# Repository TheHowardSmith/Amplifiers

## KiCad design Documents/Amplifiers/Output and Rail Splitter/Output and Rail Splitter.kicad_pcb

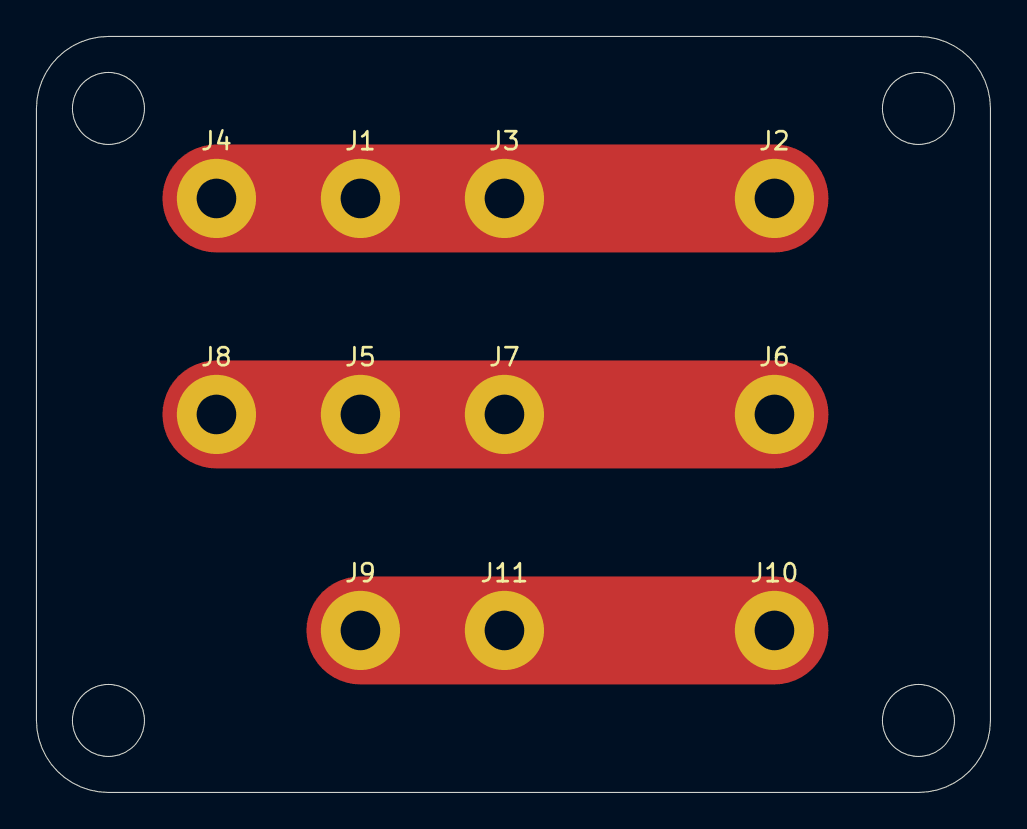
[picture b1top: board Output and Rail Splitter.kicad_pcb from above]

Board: 2 copper layers, 53.0 x 42.0 mm, 11 parts (0 on the bottom side), 3 nets.

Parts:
J1: +24V_L; MountingHole_2.2mm_M2_Pad
J2: +24V_in; MountingHole_2.2mm_M2_Pad
J3: +24V_R; MountingHole_2.2mm_M2_Pad
J4: +24V_vol; MountingHole_2.2mm_M2_Pad
J5: GND_L; MountingHole_2.2mm_M2_Pad
J6: GND_in; MountingHole_2.2mm_M2_Pad
J7: GND_R; MountingHole_2.2mm_M2_Pad
J8: GND_vol; MountingHole_2.2mm_M2_Pad
J9: -24V_L; MountingHole_2.2mm_M2_Pad
J10: -24V_in; MountingHole_2.2mm_M2_Pad
J11: -24V_R; MountingHole_2.2mm_M2_Pad

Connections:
unnamed: J1.1, J2.1, J3.1, J4.1
unnamed: J5.1, J6.1, J7.1, J8.1
unnamed: J9.1, J10.1, J11.1

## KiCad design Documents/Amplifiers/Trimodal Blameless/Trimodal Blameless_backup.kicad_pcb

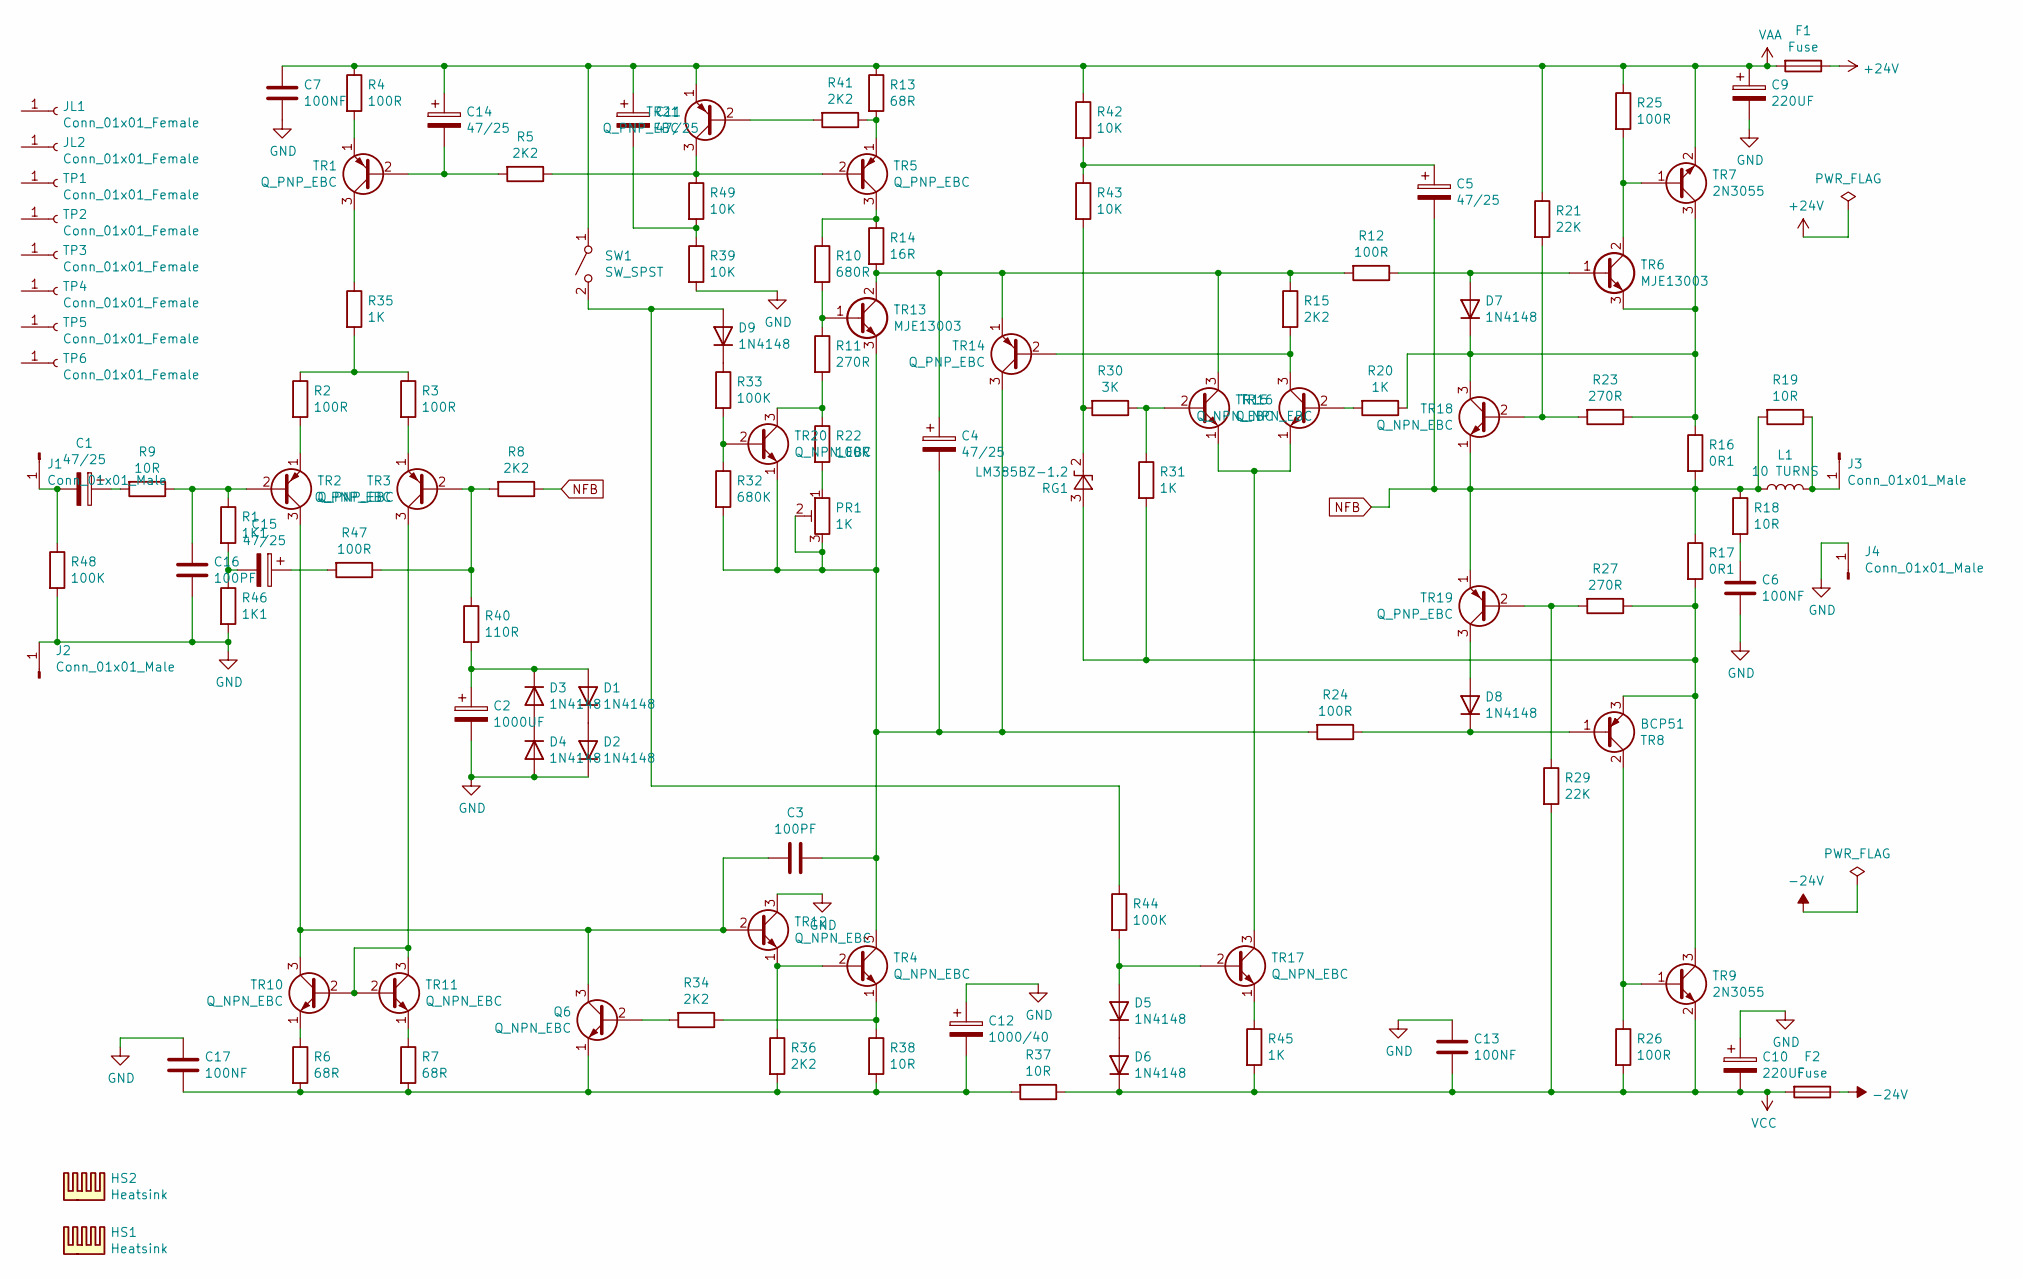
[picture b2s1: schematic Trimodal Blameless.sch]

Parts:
C1, C4, C5, C11, C14, C15: 47/25; CP_Radial_D8.0mm_P5.00mm
C2: 1000UF; CP_Radial_D10.0mm_P5.00mm
C3, C16: 100PF; C_Disc_D4.3mm_W1.9mm_P5.00mm
C6, C7, C13, C17: 100NF; C_Rect_L11.0mm_W3.5mm_P10.00mm_MKT
C9, C10: 220UF; CP_Radial_D10.0mm_P5.00mm
C12: 1000/40; CP_Radial_D12.5mm_P5.00mm
D1, D2, D3, D4, D5, D6, D7, D8, D9: 1N4148; D_DO-41_SOD81_P7.62mm_Horizontal
F1, F2: Fuse; Fuseholder_Cylinder-5x20mm_Stelvio-Kontek_PTF78_Horizontal_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
HS1, HS2: Heatsink; Heatsink_Fischer_SK104-STCB_35x13mm__2xDrill3.5mm_ScrewM3
J1, J2, J3, J4: Conn_01x01_Male; Pin_D1.3mm_L11.0mm
JL1, JL2: Conn_01x01_Female; Pin_D1.3mm_L11.0mm
L1: 10 TURNS; L_Axial_L20.3mm_D12.7mm_P25.40mm_Horizontal_Vishay_IHA-201
PR1: 1K; Potentiometer_ACP_CA9-V10_Vertical
Q6: Q_NPN_EBC; TO-92
R1, R46: 1K1; R_Axial_DIN0207_L6.3mm_D2.5mm_P10.16mm_Horizontal
R2, R3, R4, R12, R22, R24, R25, R26, R47: 100R; R_Axial_DIN0207_L6.3mm_D2.5mm_P10.16mm_Horizontal
R5, R8, R15, R34, R36, R41: 2K2; R_Axial_DIN0207_L6.3mm_D2.5mm_P10.16mm_Horizontal
R6, R7, R13: 68R; R_Axial_DIN0207_L6.3mm_D2.5mm_P10.16mm_Horizontal
R9, R18, R19, R37, R38: 10R; R_Axial_DIN0207_L6.3mm_D2.5mm_P10.16mm_Horizontal
R10: 680R; R_Axial_DIN0207_L6.3mm_D2.5mm_P10.16mm_Horizontal
R11, R23, R27: 270R; R_Axial_DIN0207_L6.3mm_D2.5mm_P10.16mm_Horizontal
R14: 16R; R_Axial_DIN0207_L6.3mm_D2.5mm_P10.16mm_Horizontal
R16, R17: 0R1; R_Axial_DIN0922_L20.0mm_D9.0mm_P30.48mm_Horizontal
R20, R31, R35, R45: 1K; R_Axial_DIN0207_L6.3mm_D2.5mm_P10.16mm_Horizontal
R21, R29: 22K; R_Axial_DIN0207_L6.3mm_D2.5mm_P10.16mm_Horizontal
R30: 3K; R_Axial_DIN0207_L6.3mm_D2.5mm_P10.16mm_Horizontal
R32: 680K; R_Axial_DIN0207_L6.3mm_D2.5mm_P10.16mm_Horizontal
R33, R44, R48: 100K; R_Axial_DIN0207_L6.3mm_D2.5mm_P10.16mm_Horizontal
R39, R42, R43, R49: 10K; R_Axial_DIN0207_L6.3mm_D2.5mm_P10.16mm_Horizontal
R40: 110R; R_Axial_DIN0207_L6.3mm_D2.5mm_P10.16mm_Horizontal
RG1: LM385BZ-1.2; TO-92_Inline
SW1: SW_SPST; SW_NKK_G1xJP
TP1, TP2, TP3, TP4, TP5, TP6: Conn_01x01_Female; Pin_D1.3mm_L11.0mm
TR1, TR2, TR3, TR5, TR14, TR19, TR21: Q_PNP_EBC; TO-92
TR4, TR10, TR11, TR12, TR15, TR16, TR17, TR18, TR20: Q_NPN_EBC; TO-92
TR6, TR13: MJE13003; TO-126-3_Vertical
TR7, TR9: 2N3055; TO-3
TR8: BCP51; TO-126-3_Vertical

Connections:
+24V: F1.1
-24V: F2.1
GND: C2.2, C6.2, C7.2, C9.2, C10.1, C12.1, C13.1, C16.2, C17.1, D2.1 (K), D4.2 (A), J2.1, J4.1, R39.2, R46.2, R48.2, TR12.3 (C)
NFB: C5.2, L1.1, R8.1, R16.2, R17.1, R18.1, R19.2, TR18.1 (E), TR19.1 (E)
unnamed: C1.1, R9.2
unnamed: C1.2, J1.1, R48.1
unnamed: C2.1, D1.2 (A), D3.1 (K), R40.2
unnamed: C3.1, C4.2, PR1.2, PR1.3, R24.2, R32.2, TR4.3 (C), TR13.3 (E), TR14.3 (C), TR20.1 (E)
unnamed: C3.2, Q6.3 (C), TR2.3 (C), TR10.3 (C), TR12.2 (B)
unnamed: C4.1, R12.2, R14.2, R15.1, TR13.2 (C), TR14.1 (E), TR15.3 (C)
unnamed: C5.1, R42.2, R43.1
unnamed: C6.1, R18.2
unnamed: C11.2, R39.1, R49.2
unnamed: C12.2, C17.2, Q6.1 (E), R6.2, R7.2, R36.2, R37.2, R38.2
unnamed: C14.2, R5.2, TR1.2 (B)
unnamed: C15.1, R47.2
unnamed: C15.2, R1.2, R46.1
unnamed: C16.1, R1.1, R9.1, TR2.2 (B)
unnamed: D1.1 (K), D2.2 (A)
unnamed: D3.2 (A), D4.1 (K)
unnamed: D5.1 (K), D6.2 (A)
unnamed: D5.2 (A), R44.2, TR17.2 (B)
unnamed: D7.1 (K), R16.1, R20.1, R23.1, TR6.3 (E), TR7.3 (C), TR18.3 (C)
unnamed: D7.2 (A), R12.1, TR6.1 (B)
unnamed: D8.1 (K), R24.1, TR8.1 (B)
unnamed: D8.2 (A), TR19.3 (C)
unnamed: D9.1 (K), R33.1
unnamed: D9.2 (A), R44.1, SW1.2 (B)
unnamed: J3.1, L1.2, R19.1
unnamed: PR1.1, R22.2
unnamed: Q6.2 (B), R34.2
unnamed: R2.1, R3.1, R35.2
unnamed: R2.2, TR2.1 (E)
unnamed: R3.2, TR3.1 (E)
unnamed: R4.2, TR1.1 (E)
unnamed: R6.1, TR10.1 (E)
unnamed: R7.1, TR11.1 (E)
unnamed: R10.1, R14.1, TR5.3 (C)
unnamed: R10.2, R11.1, TR13.1 (B)
unnamed: R11.2, R22.1, TR20.3 (C)
unnamed: R13.2, R41.1, TR5.1 (E)
unnamed: R15.2, TR14.2 (B), TR16.3 (C)
unnamed: R17.2, R27.1, R31.2, RG1.3 (A), TR8.3 (E), TR9.3 (C)
unnamed: R20.2, TR16.2 (B)
unnamed: R21.2, R23.2, TR18.2 (B)
unnamed: R25.2, TR6.2 (C), TR7.1 (B)
unnamed: R26.1, TR8.2 (C), TR9.1 (B)
unnamed: R27.2, R29.1, TR19.2 (B)
unnamed: R30.1, R31.1, TR15.2 (B)
unnamed: R30.2, R43.2, RG1.2 (K)
unnamed: R32.1, R33.2, TR20.2 (B)
unnamed: R34.1, R38.1, TR4.1 (E)
unnamed: R35.1, TR1.3 (C)
unnamed: R36.1, TR4.2 (B), TR12.1 (E)
unnamed: R8.2, R40.1, R47.1, TR3.2 (B)
unnamed: R41.2, TR21.2 (B)
unnamed: R45.1, TR17.1 (E)
unnamed: R5.1, R49.1, TR5.2 (B), TR21.3 (C)
unnamed: TR3.3 (C), TR10.2 (B), TR11.2 (B), TR11.3 (C)
unnamed: TR15.1 (E), TR16.1 (E), TR17.3 (C)
VAA: C7.1, C9.1, C11.1, C14.1, F1.2, R4.1, R13.1, R21.1, R25.1, R42.1, SW1.1 (A), TR7.2 (E), TR21.1 (E)
VCC: C10.2, C13.2, D6.1 (K), F2.2, R26.2, R29.2, R37.1, R45.2, TR9.2 (E)

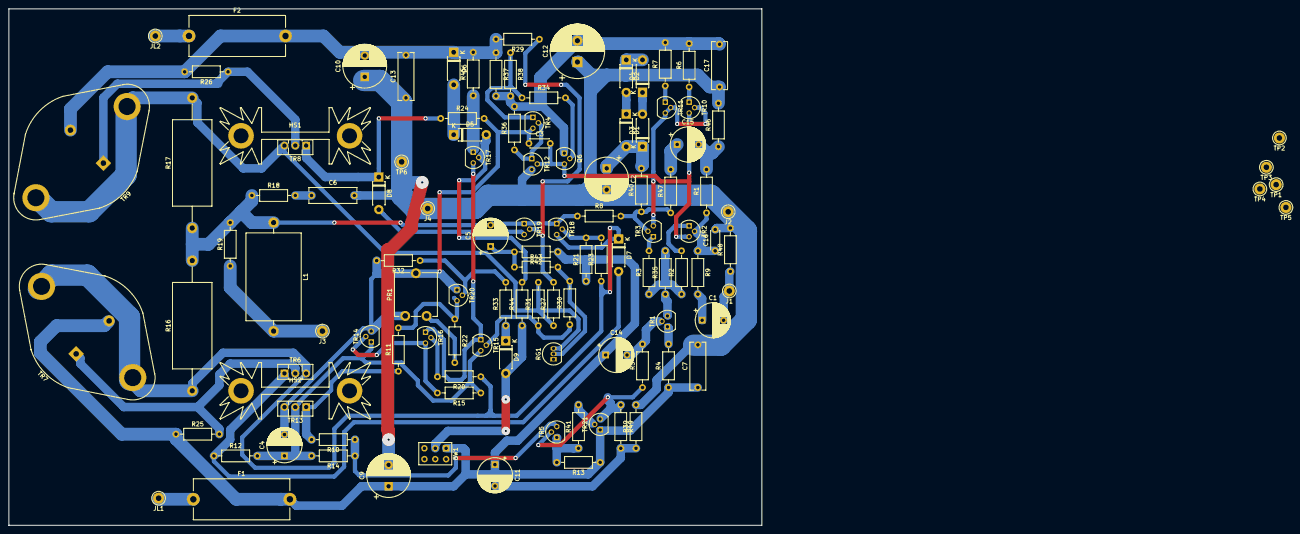
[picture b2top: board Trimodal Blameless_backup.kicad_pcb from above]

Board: 2 copper layers, 176.3 x 120.9 mm, 115 parts (0 on the bottom side), 60 nets.

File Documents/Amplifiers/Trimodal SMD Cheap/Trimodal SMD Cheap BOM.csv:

Comment,Designator,Footprint,LCSC
220UF,"C10,C9",Capacitor_SMD:CP_Elec_10x10,C176670
47/25,"C14,C1,C15,C11,C4,C5",Capacitor_Tantalum_SMD:CP_EIA-7343-31_Kemet-D,C117039
100PF,"C16,C3",Capacitor_SMD:C_0805_2012Metric,C1790
100NF,"C7,C17,C6,C13",Capacitor_SMD:C_0805_2012Metric,C49678
1N4148,"D3,D4,D1,D2,D9,D6,D5,D7,D8",Diode_SMD:D_SOD-123,C81598
1K1,"R1,R46",Resistor_SMD:R_0603_1608Metric,C22764
680R,R10,Resistor_SMD:R_0805_2012Metric,C17798
270R,"R11,R23,R27",Resistor_SMD:R_0805_2012Metric,C17590
16R,R14,Resistor_SMD:R_0805_2012Metric,C17491
0R1,"R16,R17,R166,R177",Resistor_SMD:R_2512_6332Metric,C78195
22K,"R21,R29",Resistor_SMD:R_0805_2012Metric,C17560
3K,R30,Resistor_SMD:R_0805_2012Metric,C17661
680K,R32,Resistor_SMD:R_0805_2012Metric,C17797
1K,"R35,R45,R31,R20",Resistor_SMD:R_0805_2012Metric,C17513
100R,"R4,R2,R3,R47,R24,R12,R25,R26,R22",Resistor_SMD:R_0805_2012Metric,C17408
110R,R40,Resistor_SMD:R_0805_2012Metric,C17423
100K,"R48,R33,R44",Resistor_SMD:R_0805_2012Metric,C17407
10K,"R49,R39,R42,R43",Resistor_SMD:R_0805_2012Metric,C17414
2K2,"R5,R8,R41,R36,R34,R15",Resistor_SMD:R_0805_2012Metric,C17520
68R,"R6,R7,R13",Resistor_SMD:R_0805_2012Metric,C17802
10R,"R9,R38,R37,R18,R19",Resistor_SMD:R_0805_2012Metric,C17415
LM385M3X-2.5,RG1,Package_TO_SOT_SMD:SOT-23,C83345
SW_SPST,SW1,Package_SO:SOP-4_3.8x4.1mm_P2.54mm,C99477
Q_PNP_EBC,"TR1,TR3,TR2,TR21,TR5,TR14,TR19",Package_TO_SOT_SMD:SOT-89-3,C47787
Q_NPN_EBC,"TR10,TR11,TR20,TR4,TR12,Q6,TR15,TR16,TR18,TR17",Package_TO_SOT_SMD:SOT-89-3,C100026

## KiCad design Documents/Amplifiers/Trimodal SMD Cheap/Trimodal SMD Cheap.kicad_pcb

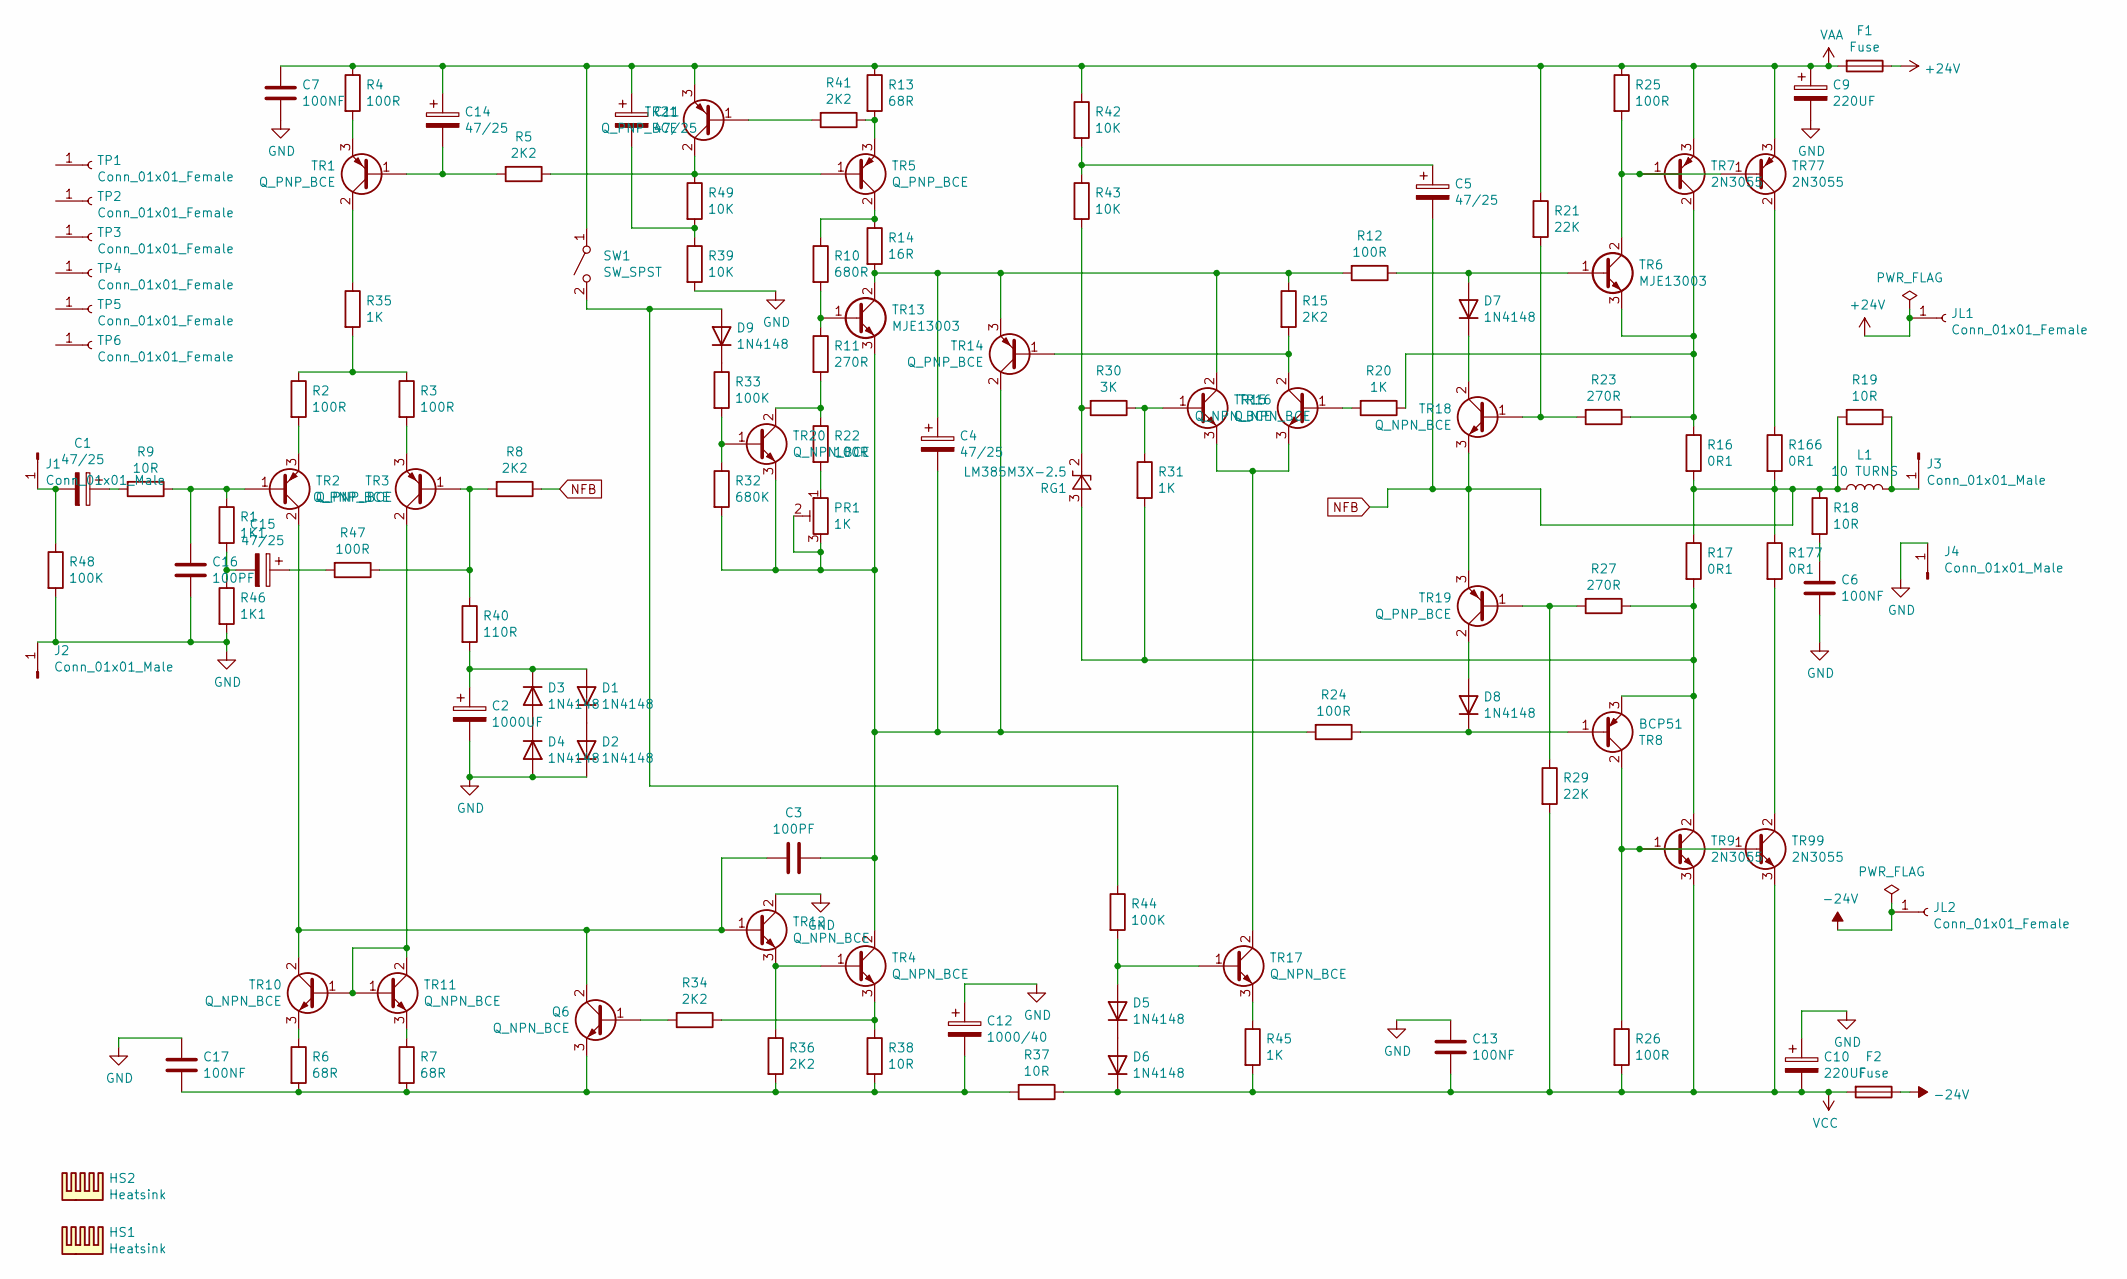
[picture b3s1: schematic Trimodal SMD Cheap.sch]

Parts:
C1, C4, C5, C11, C14, C15: 47/25; CP_EIA-7343-31_Kemet-D
C2: 1000UF; CP_Radial_D12.5mm_P5.00mm
C3, C16: 100PF; C_0805_2012Metric
C6, C7, C13, C17: 100NF; C_0805_2012Metric
C9, C10: 220UF; CP_Elec_10x10
C12: 1000/40; CP_Radial_D12.5mm_P5.00mm
D1, D2, D3, D4, D5, D6, D7, D8, D9: 1N4148; D_SOD-123
F1, F2: Fuse; Fuseholder_Cylinder-5x20mm_Stelvio-Kontek_PTF78_Horizontal_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
HS1, HS2: Heatsink; Heatsink_Fischer_SK104-STCB_35x13mm__2xDrill3.5mm_ScrewM3
J1, J2: Conn_01x01_Male; Pin_D1.3mm_L11.0mm
J3, J4: Conn_01x01_Male; MountingHole_2.2mm_M2_Pad
JL1, JL2: Conn_01x01_Female; MountingHole_2.2mm_M2_Pad
L1: 10 TURNS; L_Axial_L20.3mm_D12.7mm_P25.40mm_Horizontal_Vishay_IHA-201
PR1: 1K; Potentiometer_ACP_CA9-V10_Vertical
Q6: Q_NPN_BCE; SOT-89-3
R1, R46: 1K1; R_0805_2012Metric
R2, R3, R4, R12, R22, R24, R25, R26, R47: 100R; R_0805_2012Metric
R5, R8, R15, R34, R36, R41: 2K2; R_0805_2012Metric
R6, R7, R13: 68R; R_0805_2012Metric
R9, R18, R19, R37, R38: 10R; R_0805_2012Metric
R10: 680R; R_0805_2012Metric
R11, R23, R27: 270R; R_0805_2012Metric
R14: 16R; R_0805_2012Metric
R16, R17, R166, R177: 0R1; R_2512_6332Metric
R20, R31, R35, R45: 1K; R_0805_2012Metric
R21, R29: 22K; R_0805_2012Metric
R30: 3K; R_0805_2012Metric
R32: 680K; R_0805_2012Metric
R33, R44, R48: 100K; R_0805_2012Metric
R39, R42, R43, R49: 10K; R_0805_2012Metric
R40: 110R; R_0805_2012Metric
RG1: LM385M3X-2.5; SOT-23
SW1: SW_SPST; SOP-4_3.8x4.1mm_P2.54mm
TP1, TP2: Conn_01x01_Female; Pin_D1.3mm_L11.0mm
TP3, TP4, TP5, TP6: Conn_01x01_Female; MountingHole_2.2mm_M2_Pad
TR1, TR2, TR3, TR5, TR14, TR19, TR21: Q_PNP_BCE; SOT-89-3
TR4, TR10, TR11, TR12, TR15, TR16, TR17, TR18, TR20: Q_NPN_BCE; SOT-89-3
TR6, TR13: MJE13003; TO-126-3_Vertical
TR7, TR9, TR77, TR99: 2N3055; TO-3P-3_Vertical
TR8: BCP51; TO-126-3_Vertical

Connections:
+24V: F1.1, JL1.1
-24V: F2.1, JL2.1
GND: C2.2, C6.2, C7.2, C9.2, C10.1, C12.1, C13.1, C16.2, C17.1, D2.1 (K), D4.2 (A), J2.1, J4.1, R39.2, R46.2, R48.2, TR12.2 (C)
NFB: C5.2, L1.1, R8.1, R16.2, R17.1, R18.1, R19.2, R166.2, R177.1, TR18.3 (E), TR19.3 (E)
unnamed: C1.1, R9.2
unnamed: C1.2, J1.1, R48.1
unnamed: C2.1, D1.2 (A), D3.1 (K), R40.2
unnamed: C3.1, C4.2, PR1.2, PR1.3, R24.2, R32.2, TR4.2 (C), TR13.3 (E), TR14.2 (C), TR20.3 (E)
unnamed: C3.2, Q6.2 (C), TR2.2 (C), TR10.2 (C), TR12.1 (B)
unnamed: C4.1, R12.2, R14.2, R15.1, TR13.2 (C), TR14.3 (E), TR15.2 (C)
unnamed: C5.1, R42.2, R43.1
unnamed: C6.1, R18.2
unnamed: C11.2, R39.1, R49.2
unnamed: C12.2, C17.2, Q6.3 (E), R6.2, R7.2, R36.2, R37.2, R38.2
unnamed: C14.2, R5.2, TR1.1 (B)
unnamed: C15.1, R47.2
unnamed: C15.2, R1.2, R46.1
unnamed: C16.1, R1.1, R9.1, TR2.1 (B)
unnamed: D1.1 (K), D2.2 (A)
unnamed: D3.2 (A), D4.1 (K)
unnamed: D5.1 (K), D6.2 (A)
unnamed: D5.2 (A), R44.2, TR17.1 (B)
unnamed: D7.1 (K), TR18.2 (C)
unnamed: D7.2 (A), R12.1, TR6.1 (B)
unnamed: D8.1 (K), R24.1, TR8.1 (B)
unnamed: D8.2 (A), TR19.2 (C)
unnamed: D9.1 (K), R33.1
unnamed: D9.2 (A), R44.1, SW1.2 (B)
unnamed: J3.1, L1.2, R19.1
unnamed: PR1.1, R22.2
unnamed: Q6.1 (B), R34.2
unnamed: R2.1, R3.1, R35.2
unnamed: R2.2, TR2.3 (E)
unnamed: R3.2, TR3.3 (E)
unnamed: R4.2, TR1.3 (E)
unnamed: R6.1, TR10.3 (E)
unnamed: R7.1, TR11.3 (E)
unnamed: R10.1, R14.1, TR5.2 (C)
unnamed: R10.2, R11.1, TR13.1 (B)
unnamed: R11.2, R22.1, TR20.2 (C)
unnamed: R13.2, R41.1, TR5.3 (E)
unnamed: R15.2, TR14.1 (B), TR16.2 (C)
unnamed: R16.1, R20.1, R23.1, TR6.3 (E), TR7.2 (C)
unnamed: R17.2, R27.1, R31.2, RG1.3 (A), TR8.3 (E), TR9.2 (C)
unnamed: R20.2, TR16.1 (B)
unnamed: R21.2, R23.2, TR18.1 (B)
unnamed: R25.2, TR6.2 (C), TR7.1 (B), TR77.1 (B)
unnamed: R26.1, TR8.2 (C), TR9.1 (B), TR99.1 (B)
unnamed: R27.2, R29.1, TR19.1 (B)
unnamed: R30.1, R31.1, TR15.1 (B)
unnamed: R30.2, R43.2, RG1.2 (K)
unnamed: R32.1, R33.2, TR20.1 (B)
unnamed: R34.1, R38.1, TR4.3 (E)
unnamed: R35.1, TR1.2 (C)
unnamed: R36.1, TR4.1 (B), TR12.3 (E)
unnamed: R8.2, R40.1, R47.1, TR3.1 (B)
unnamed: R41.2, TR21.1 (B)
unnamed: R45.1, TR17.3 (E)
unnamed: R5.1, R49.1, TR5.1 (B), TR21.2 (C)
unnamed: R166.1, TR77.2 (C)
unnamed: R177.2, TR99.2 (C)
unnamed: TR3.2 (C), TR10.1 (B), TR11.1 (B), TR11.2 (C)
unnamed: TR15.3 (E), TR16.3 (E), TR17.2 (C)
VAA: C7.1, C9.1, C11.1, C14.1, F1.2, R4.1, R13.1, R21.1, R25.1, R42.1, SW1.1 (A), TR7.3 (E), TR21.3 (E), TR77.3 (E)
VCC: C10.2, C13.2, D6.1 (K), F2.2, R26.2, R29.2, R37.1, R45.2, TR9.3 (E), TR99.3 (E)

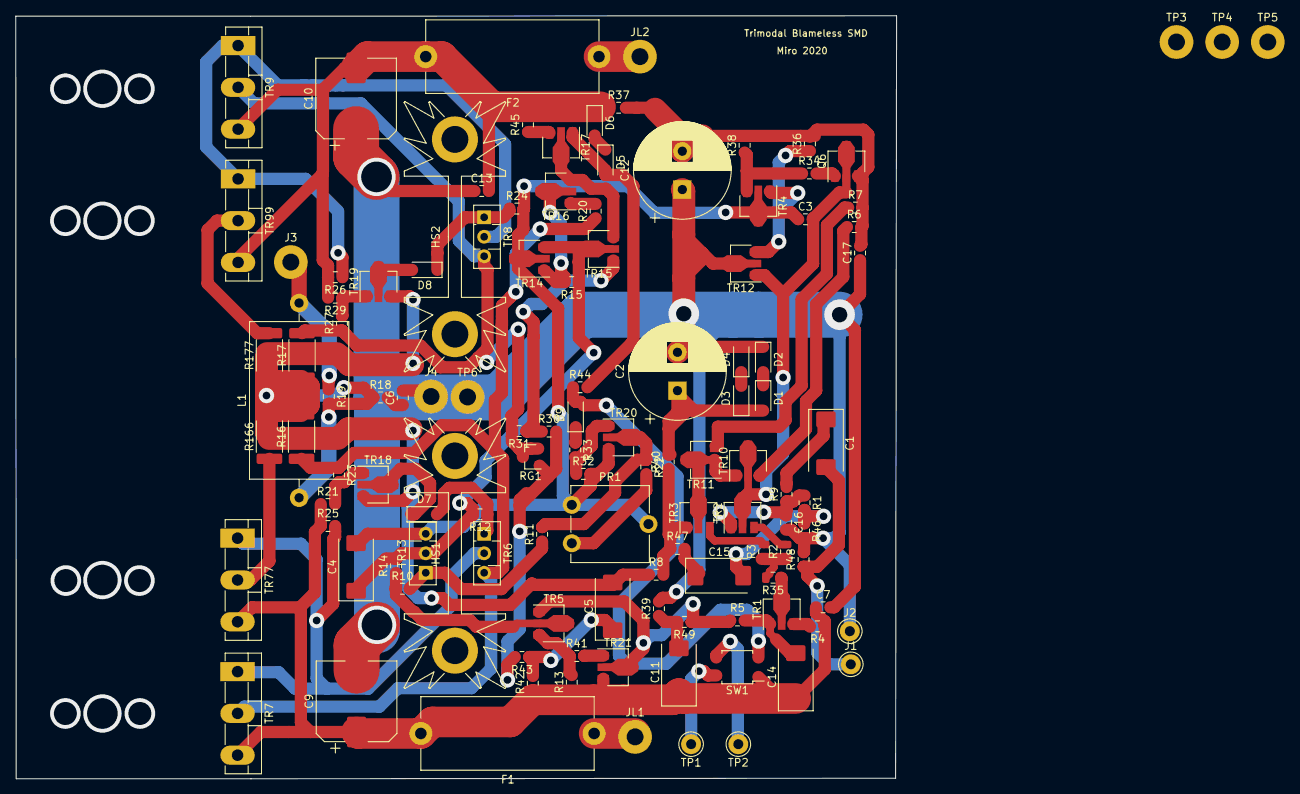
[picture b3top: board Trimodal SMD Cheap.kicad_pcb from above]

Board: 2 copper layers, 114.9 x 99.5 mm, 119 parts (0 on the bottom side), 65 nets.

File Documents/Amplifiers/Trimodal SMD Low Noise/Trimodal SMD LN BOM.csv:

Comment,Designator,Footprint,LCSC
220UF,"C10,C9",Capacitor_SMD:CP_Elec_10x10,C176670
47/25,"C14,C1,C15,C11,C4,C5",Capacitor_SMD:CP_Elec_6.3x5.3,C249976
100PF,"C16,C3",Capacitor_SMD:C_0805_2012Metric,C1790
100NF,"C7,C17,C6,C13",Capacitor_SMD:C_0805_2012Metric,C49678
1N4148,"D3,D4,D1,D2,D9,D6,D5,D7,D8",Diode_SMD:D_SOD-123,C81598
1K1,"R1,R46",Resistor_SMD:R_0805_2012Metric,
680R,R10,Resistor_SMD:R_0805_2012Metric,
270R,"R11,R23,R27",Resistor_SMD:R_0805_2012Metric,
16R,R14,Resistor_SMD:R_0805_2012Metric,
0R1,"R16,R17,R166,R177",Resistor_SMD:R_2512_6332Metric,C78195
22K,"R21,R29",Resistor_SMD:R_0805_2012Metric,
3K,R30,Resistor_SMD:R_0805_2012Metric,
680K,R32,Resistor_SMD:R_0805_2012Metric,
1K,"R35,R45,R31,R20",Resistor_SMD:R_0805_2012Metric,
100R,"R4,R2,R3,R47,R24,R12,R25,R26,R22",Resistor_SMD:R_0805_2012Metric,
110R,R40,Resistor_SMD:R_0805_2012Metric,
100K,"R48,R33,R44",Resistor_SMD:R_0805_2012Metric,
10K,"R49,R39,R42,R43",Resistor_SMD:R_0805_2012Metric,
2K2,"R5,R8,R41,R36,R34,R15",Resistor_SMD:R_0805_2012Metric,
68R,"R6,R7,R13",Resistor_SMD:R_0805_2012Metric,
10R,"R9,R38,R37,R18,R19",Resistor_SMD:R_0805_2012Metric,
LM385M3X-2.5,RG1,Package_TO_SOT_SMD:SOT-23,C83345
SW_SPST,SW1,Package_SO:SOP-4_3.8x4.1mm_P2.54mm,C459807
Q_PNP_EBC,"TR1,TR3,TR2,TR21,TR5,TR14,TR19",Package_TO_SOT_SMD:SOT-89-3,C24278
Q_NPN_EBC,"TR10,TR11,TR20,TR4,TR12,Q6,TR15,TR16,TR18,TR17",Package_TO_SOT_SMD:SOT-89-3,C9634
